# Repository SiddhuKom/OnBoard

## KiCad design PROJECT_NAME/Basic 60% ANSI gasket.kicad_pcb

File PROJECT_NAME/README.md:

---
name: "Isaiah Robertson"
slack_handle: "@SLACK HANDLE"
github_handle: "@SiddhuKom"
tutorial: # Link to the tutorial if you used one
---

# YOUR PROJECT NAME

<!-- Its a keyboard PCb that takes in keypresses and sents it to the computer -->

<!-- £115 with shipping but £98.10 without -->

<!-- Tell us a little bit about your design process. What were some challenges? What helped? ***Totally optional*** -->

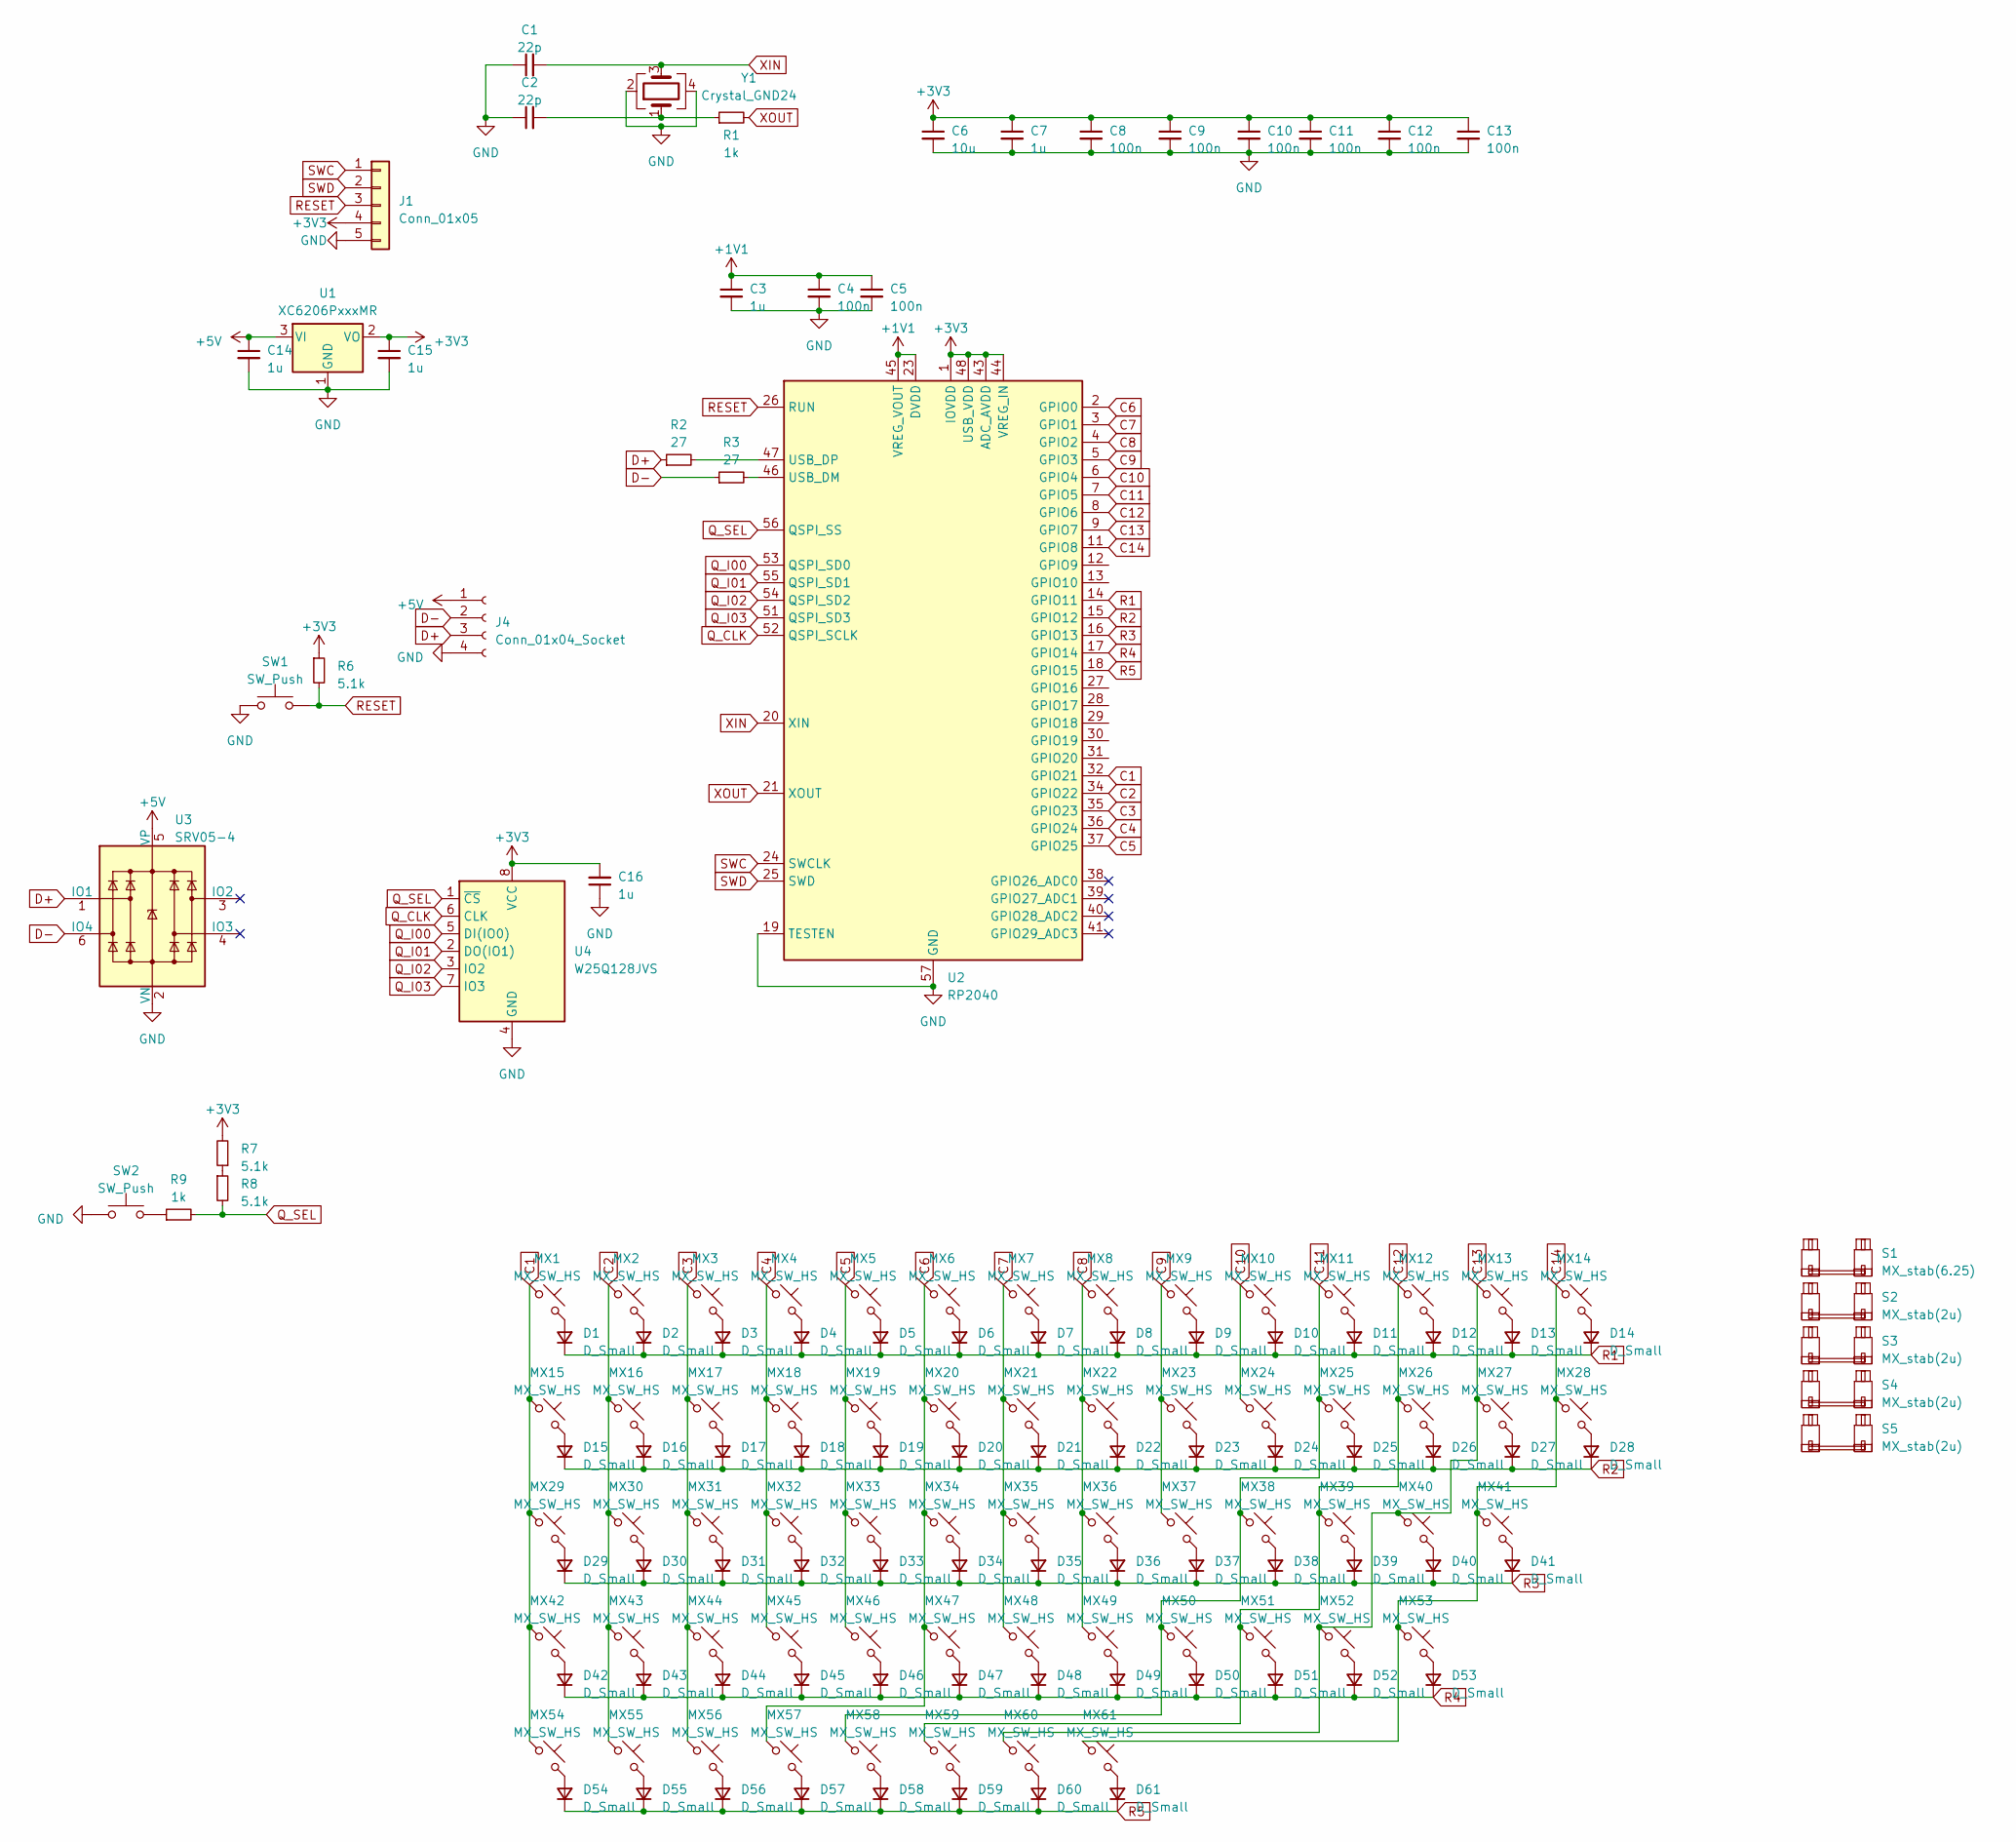
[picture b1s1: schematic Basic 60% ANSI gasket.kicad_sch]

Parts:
C1, C2: 22p; C_0402_1005Metric
C3, C7, C14, C15, C16: 1u; C_0402_1005Metric
C4, C5, C8, C9, C10, C11, C12, C13: 100n; C_0402_1005Metric
C6: 10u; C_0603_1608Metric
D1, D2, D3, D4, D5, D6, D7, D8, D9, D10, D11, D12, D13, D14, D15, D16, D17, D18, D19, D20, D21, D22, D23, D24, D25, D26, D27, D28, D29, D30, D31, D32, D33, D34, D35, D36, D37, D38, D39, D40, D41, D42, D43, D44, D45, D46, D47, D48, D49, D50, D51, D52, D53, D54, D55, D56, D57, D58, D59, D60, D61: D_Small; D_SOD-123
J1: Conn_01x05; PinHeader_1x05_P2.54mm_Vertical
J4: Conn_01x04_Socket; Molex_Pico-EZmate_78171-0004_1x04-1MP_P1.20mm_Vertical
MX1, MX2, MX3, MX4, MX5, MX6, MX7, MX8, MX9, MX10, MX11, MX12, MX13, MX14, MX16, MX17, MX18, MX19, MX20, MX21, MX22, MX23, MX24, MX25, MX26, MX27, MX30, MX31, MX32, MX33, MX34, MX35, MX36, MX37, MX38, MX39, MX40, MX41, MX42, MX43, MX44, MX45, MX46, MX47, MX48, MX49, MX50, MX51, MX52, MX53, MX57: MX_SW_HS; SW_MX_1u
MX15, MX28: MX_SW_HS; SW_MX_1.5u
MX29: MX_SW_HS; SW_MX_1.75u
MX54, MX55, MX56, MX58, MX59, MX60, MX61: MX_SW_HS; SW_MX_1.25u
R1, R9: 1k; R_0402_1005Metric
R2, R3: 27; R_0402_1005Metric
R6, R7, R8: 5.1k; R_0402_1005Metric
S1: MX_stab(6.25); STAB_MX_P_6.25u
S2, S4: MX_stab(2u); STAB_MX_P_2.25u
S3: MX_stab(2u); STAB_MX_P_2.75u
S5: MX_stab(2u); STAB_MX_P_2u
SW1, SW2: SW_Push; SW_SPST_SKQG_WithoutStem
U1: XC6206PxxxMR; SOT-23-3
U2: RP2040; QFN-56-1EP_7x7mm_P0.4mm_EP3.2x3.2mm
U3: SRV05-4; SOT-23-6-routable
U4: W25Q128JVS; SOIC-8_5.23x5.23mm_P1.27mm
Y1: Crystal_GND24; Crystal_SMD_3225-4Pin_3.2x2.5mm

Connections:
+5V: C14.1, J4.1, U1.3 (VI)
C1: MX1.1, MX15.1, MX29.1, MX42.1, MX54.1, U2.32 (GPIO21)
C2: MX2.1, MX16.1, MX30.1, MX43.1, MX55.1, U2.34 (GPIO22)
C3: MX3.1, MX17.1, MX31.1, MX44.1, MX56.1, U2.35 (GPIO23)
C4: MX4.1, MX18.1, MX32.1, MX45.1, U2.36 (GPIO24)
C5: MX5.1, MX19.1, MX33.1, MX46.1, U2.37 (GPIO25)
C6: MX6.1, MX20.1, MX34.1, MX47.1, MX57.1, U2.2 (GPIO0)
C7: MX7.1, MX21.1, MX35.1, MX48.1, U2.3 (GPIO1)
C8: MX8.1, MX22.1, MX36.1, MX49.1, U2.4 (GPIO2)
C9: MX9.1, MX23.1, MX37.1, U2.5 (GPIO3)
C10: MX10.1, MX24.1, U2.6 (GPIO4)
C11: MX11.1, MX25.1, MX38.1, MX50.1, MX58.1, U2.7 (GPIO5)
C12: MX12.1, MX26.1, MX39.1, MX51.1, MX59.1, U2.8 (GPIO6)
C13: MX13.1, MX27.1, MX40.1, MX52.1, MX60.1, U2.9 (GPIO7)
C14: MX14.1, MX28.1, MX41.1, MX53.1, MX61.1, U2.11 (GPIO8)
D+: J4.3, R2.1, U3.1 (IO1)
D-: J4.2, R3.1, U3.6 (IO4)
GND: C1.1, C2.1, C3.2, C4.2, C5.2, C6.2, C7.2, C8.2, C9.2, C10.2, C11.2, C12.2, C13.2, C14.2, C15.2, C16.1, J1.5, J4.4, SW1.1, SW2.1, U1.1 (GND), U2.19 (TESTEN), U2.57 (GND), U4.4 (GND), Y1.2, Y1.4
unnamed: C2.2, R1.1, Y1.1
unnamed: D1.2 (A), MX1.2
unnamed: D2.2 (A), MX2.2
unnamed: D3.2 (A), MX3.2
unnamed: D4.2 (A), MX4.2
unnamed: D5.2 (A), MX5.2
unnamed: D6.2 (A), MX6.2
unnamed: D7.2 (A), MX7.2
unnamed: D8.2 (A), MX8.2
unnamed: D9.2 (A), MX9.2
unnamed: D10.2 (A), MX10.2
unnamed: D11.2 (A), MX11.2
unnamed: D12.2 (A), MX12.2
unnamed: D13.2 (A), MX13.2
unnamed: D14.2 (A), MX14.2
unnamed: D15.2 (A), MX15.2
unnamed: D16.2 (A), MX16.2
unnamed: D17.2 (A), MX17.2
unnamed: D18.2 (A), MX18.2
unnamed: D19.2 (A), MX19.2
unnamed: D20.2 (A), MX20.2
unnamed: D21.2 (A), MX21.2
unnamed: D22.2 (A), MX22.2
unnamed: D23.2 (A), MX23.2
unnamed: D24.2 (A), MX24.2
unnamed: D25.2 (A), MX25.2
unnamed: D26.2 (A), MX26.2
unnamed: D27.2 (A), MX27.2
unnamed: D28.2 (A), MX28.2
unnamed: D29.2 (A), MX29.2
unnamed: D30.2 (A), MX30.2
unnamed: D31.2 (A), MX31.2
unnamed: D32.2 (A), MX32.2
unnamed: D33.2 (A), MX33.2
unnamed: D34.2 (A), MX34.2
unnamed: D35.2 (A), MX35.2
unnamed: D36.2 (A), MX36.2
unnamed: D37.2 (A), MX37.2
unnamed: D38.2 (A), MX38.2
unnamed: D39.2 (A), MX39.2
unnamed: D40.2 (A), MX40.2
unnamed: D41.2 (A), MX41.2
unnamed: D42.2 (A), MX42.2
unnamed: D43.2 (A), MX43.2
unnamed: D44.2 (A), MX44.2
unnamed: D45.2 (A), MX45.2
unnamed: D46.2 (A), MX46.2
unnamed: D47.2 (A), MX47.2
unnamed: D48.2 (A), MX48.2
unnamed: D49.2 (A), MX49.2
unnamed: D50.2 (A), MX50.2
unnamed: D51.2 (A), MX51.2
unnamed: D52.2 (A), MX52.2
unnamed: D53.2 (A), MX53.2
unnamed: D54.2 (A), MX54.2
unnamed: D55.2 (A), MX55.2
unnamed: D56.2 (A), MX56.2
unnamed: D57.2 (A), MX57.2
unnamed: D58.2 (A), MX58.2
unnamed: D59.2 (A), MX59.2
unnamed: D60.2 (A), MX60.2
unnamed: D61.2 (A), MX61.2
unnamed: R7.1, R8.1
unnamed: R9.1, SW2.2
unnamed: R3.2, U2.46 (USB_DM)
unnamed: R2.2, U2.47 (USB_DP)
Q_CLK: U2.52 (QSPI_SCLK), U4.6 (CLK)
Q_I00: U2.53 (QSPI_SD0), U4.5 (DI(IO0))
Q_I01: U2.55 (QSPI_SD1), U4.2 (DO(IO1))
Q_I02: U2.54 (QSPI_SD2), U4.3 (IO2)
Q_I03: U2.51 (QSPI_SD3), U4.7 (IO3)
Q_SEL: R8.2, R9.2, U2.56 (QSPI_SS), U4.1 (~CS)
R1: D1.1 (K), D2.1 (K), D3.1 (K), D4.1 (K), D5.1 (K), D6.1 (K), D7.1 (K), D8.1 (K), D9.1 (K), D10.1 (K), D11.1 (K), D12.1 (K), D13.1 (K), D14.1 (K), U2.14 (GPIO11)
R2: D15.1 (K), D16.1 (K), D17.1 (K), D18.1 (K), D19.1 (K), D20.1 (K), D21.1 (K), D22.1 (K), D23.1 (K), D24.1 (K), D25.1 (K), D26.1 (K), D27.1 (K), D28.1 (K), U2.15 (GPIO12)
R3: D29.1 (K), D30.1 (K), D31.1 (K), D32.1 (K), D33.1 (K), D34.1 (K), D35.1 (K), D36.1 (K), D37.1 (K), D38.1 (K), D39.1 (K), D40.1 (K), D41.1 (K), U2.16 (GPIO13)
R4: D42.1 (K), D43.1 (K), D44.1 (K), D45.1 (K), D46.1 (K), D47.1 (K), D48.1 (K), D49.1 (K), D50.1 (K), D51.1 (K), D52.1 (K), D53.1 (K), U2.17 (GPIO14)
R5: D54.1 (K), D55.1 (K), D56.1 (K), D57.1 (K), D58.1 (K), D59.1 (K), D60.1 (K), D61.1 (K), U2.18 (GPIO15)
RESET: J1.3, R6.2, SW1.2, U2.26 (RUN)
SWC: J1.1, U2.24 (SWCLK)
SWD: J1.2, U2.25 (SWD)
XIN: C1.2, U2.20 (XIN), Y1.3
XOUT: R1.2, U2.21 (XOUT)

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
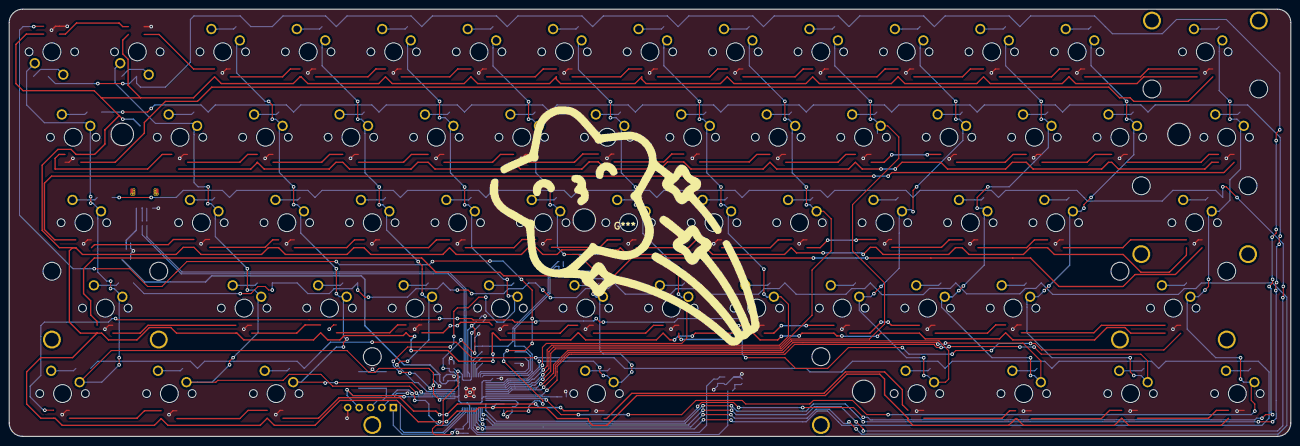
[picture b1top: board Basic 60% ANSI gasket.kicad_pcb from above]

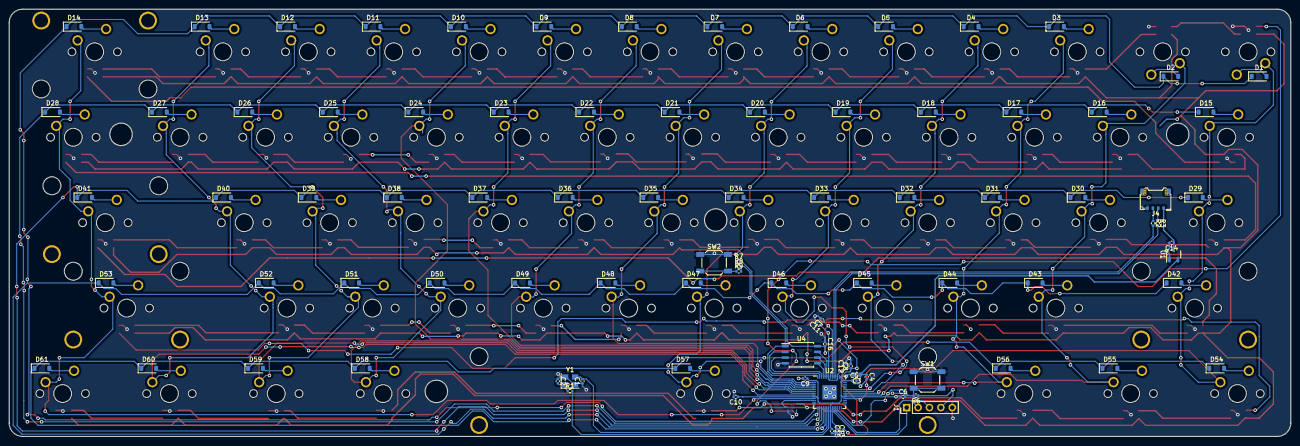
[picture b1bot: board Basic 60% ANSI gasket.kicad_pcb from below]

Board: 2 copper layers, 285.8 x 95.2 mm, 158 parts (158 on the bottom side), 102 nets.
